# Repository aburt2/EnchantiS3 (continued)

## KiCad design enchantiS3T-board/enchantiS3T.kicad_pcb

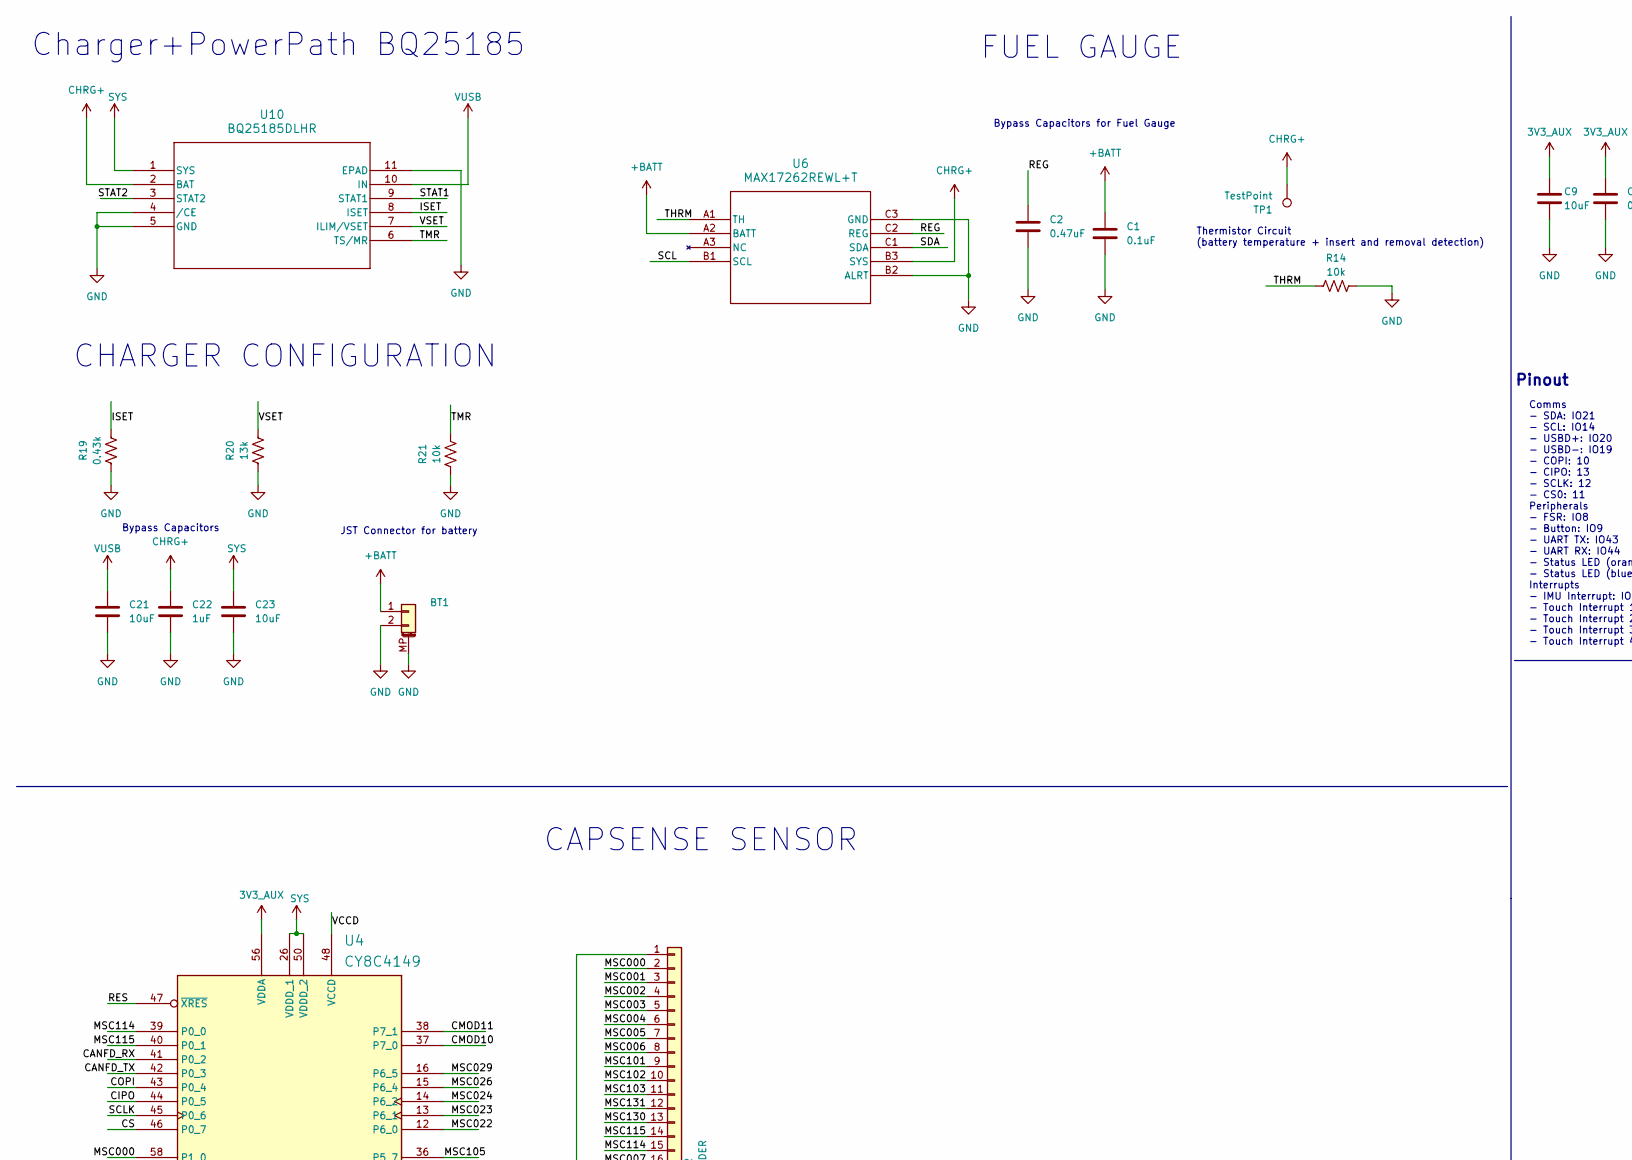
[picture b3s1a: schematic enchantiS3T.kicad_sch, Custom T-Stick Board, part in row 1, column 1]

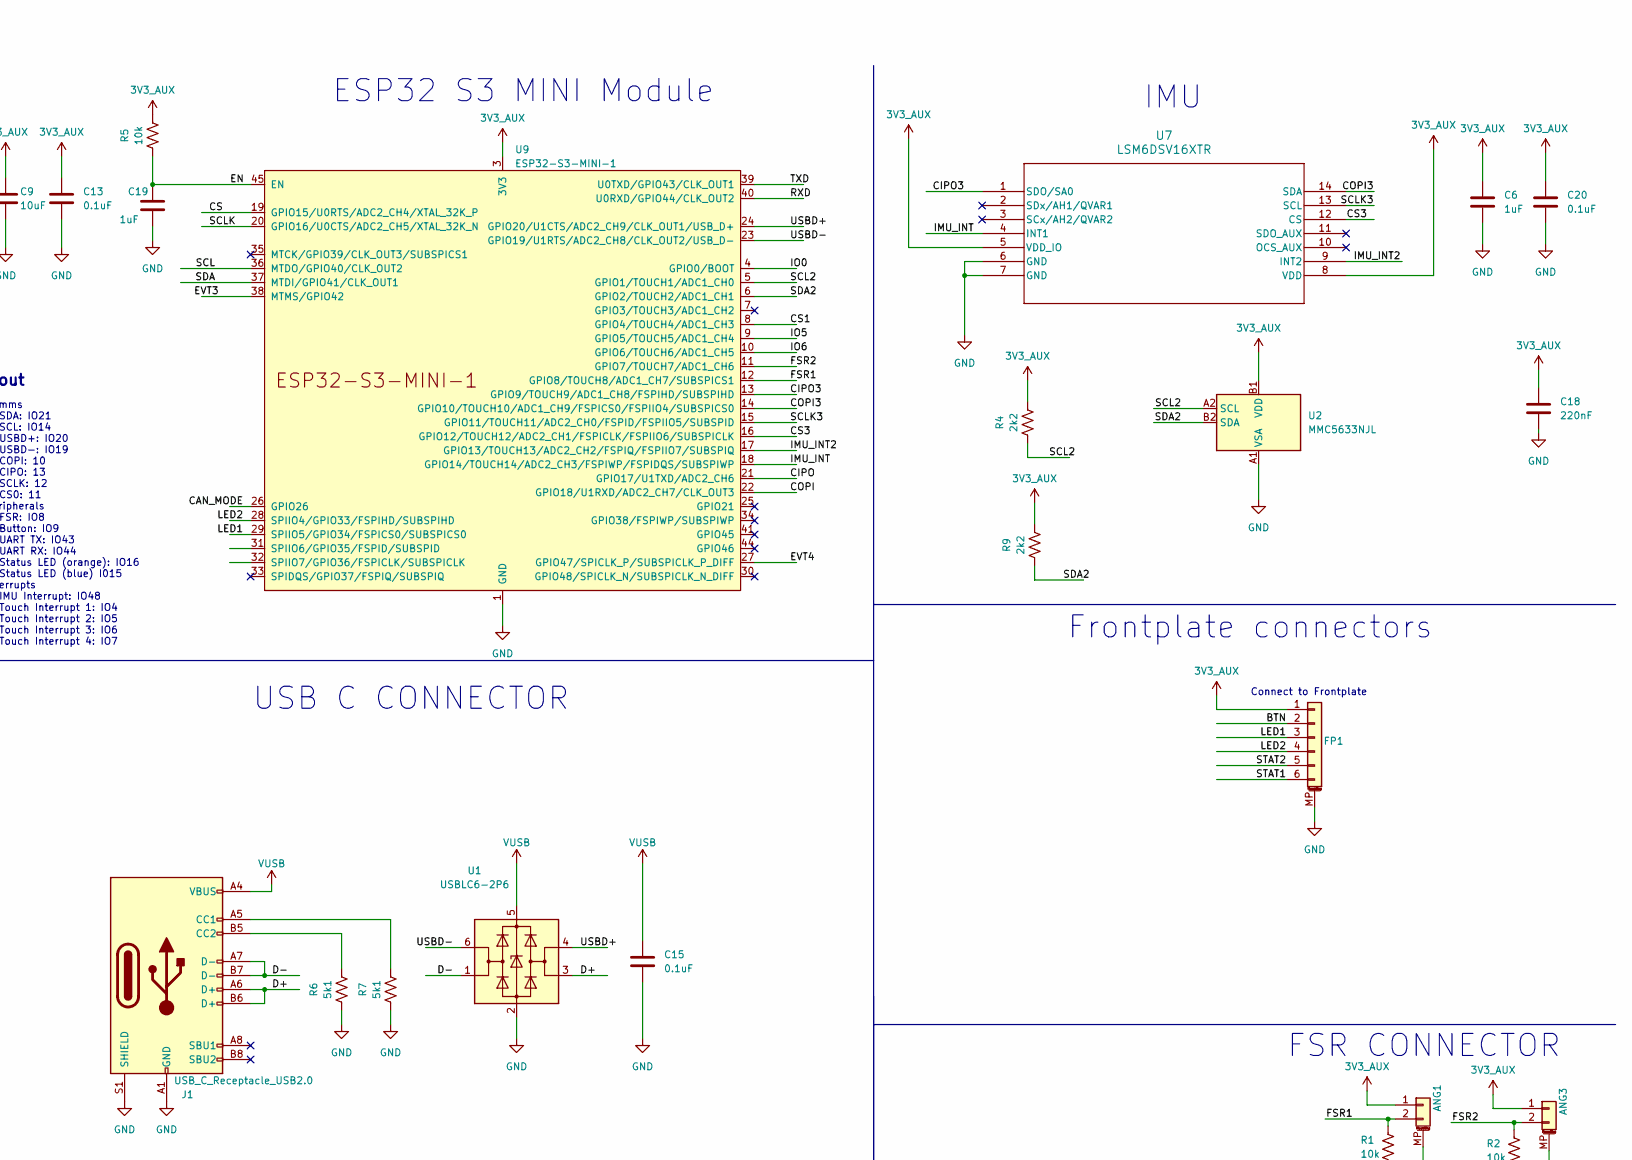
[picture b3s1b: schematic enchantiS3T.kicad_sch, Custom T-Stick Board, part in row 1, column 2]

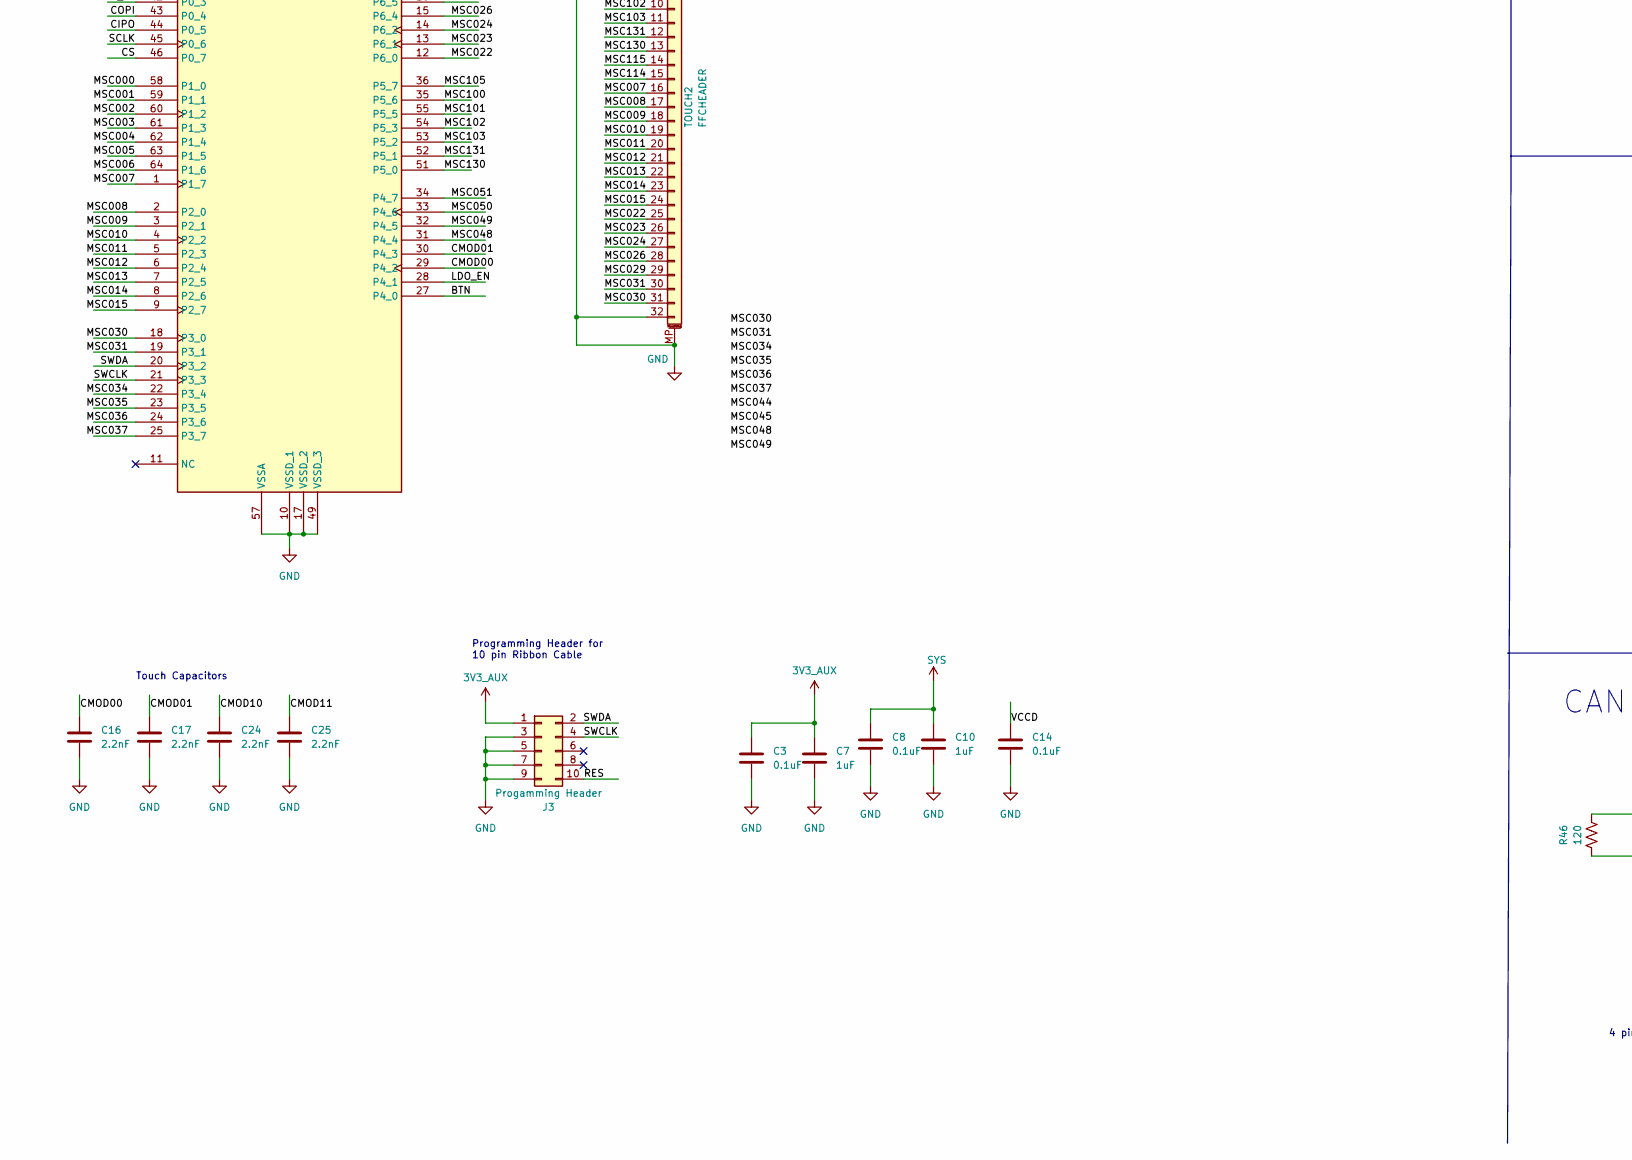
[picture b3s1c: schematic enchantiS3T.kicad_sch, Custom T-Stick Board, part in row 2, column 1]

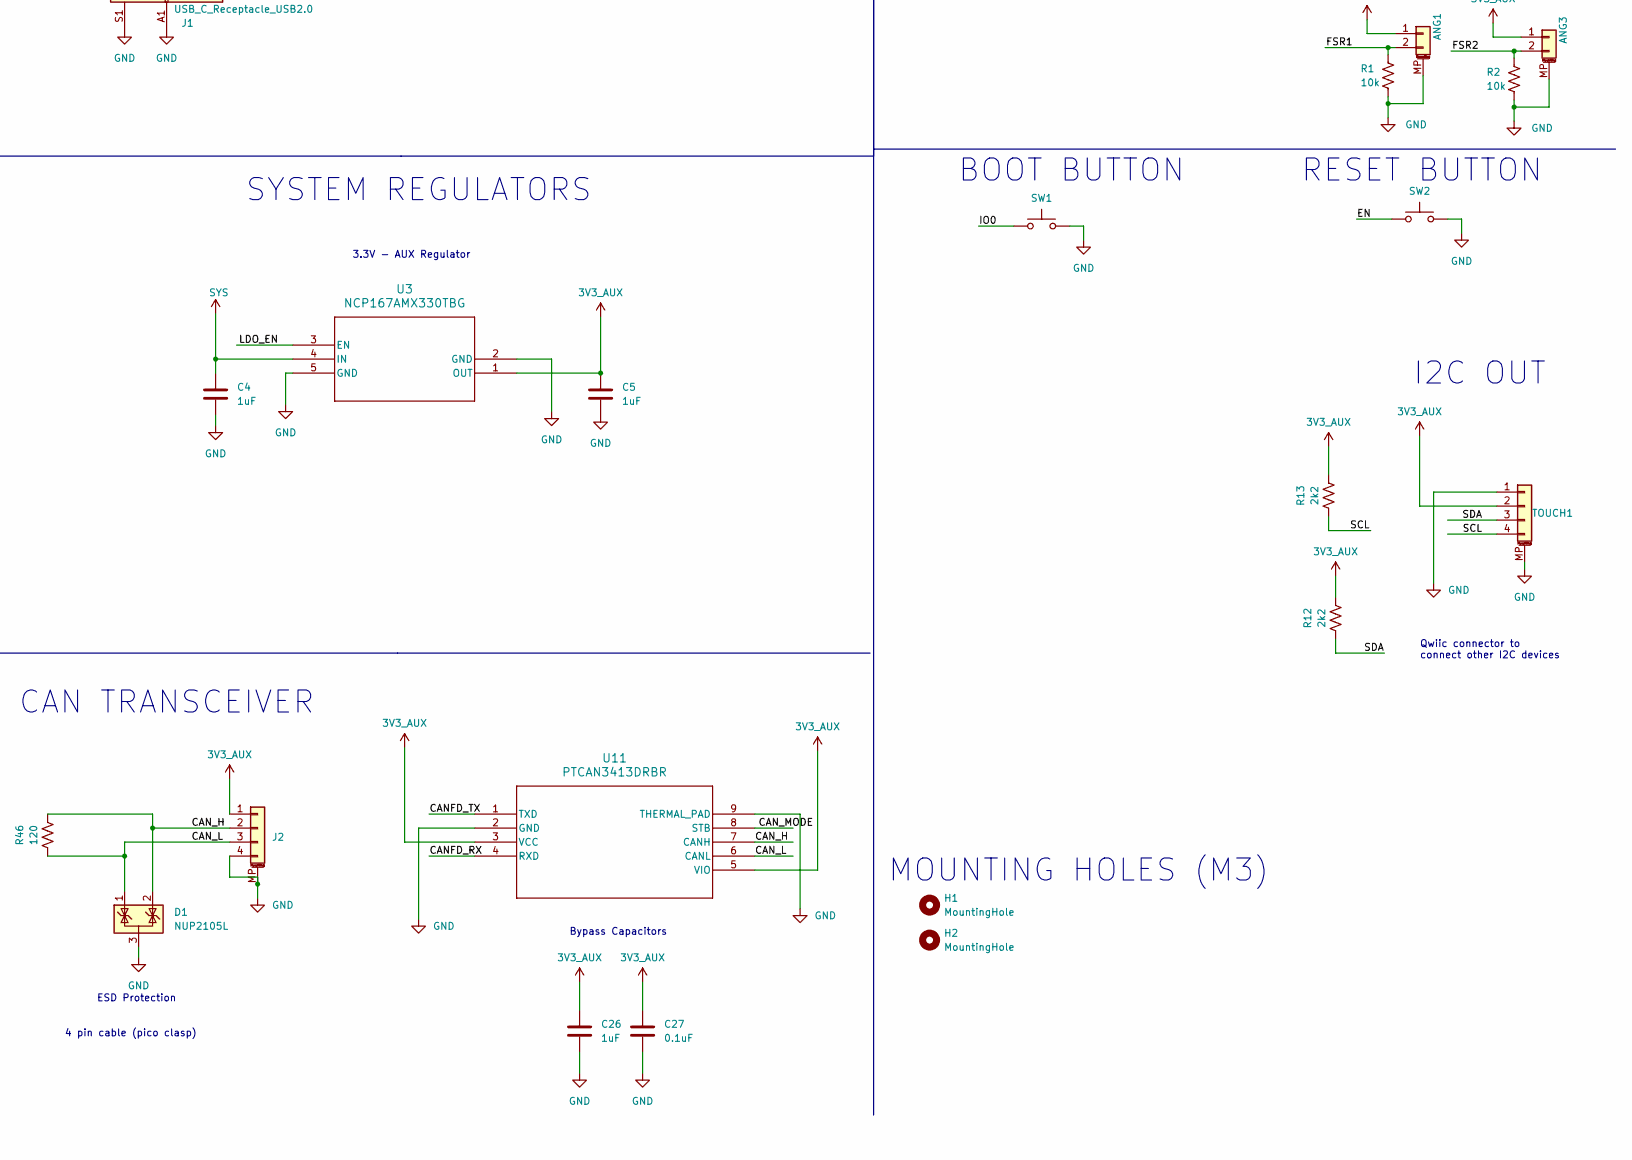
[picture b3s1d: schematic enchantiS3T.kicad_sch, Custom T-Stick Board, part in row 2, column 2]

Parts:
ANG1, ANG3: JST-SH-1.00mm 1x2; JST_SH_BM02B-SRSS-TB_1x02-1MP_P1.00mm_Vertical; Mfg Part # BM02B-SRSS-TB
BT1: JST-PH-1x02-2.000mm; JST_PH_S2B-PH-SM4-TB_1x02-1MP_P2.00mm_Horizontal; Mfg Part # S2B-PH-SM4-TB
C1, C13, C15, C20, C27: 0.1uF; C_0402_1005Metric; Mfg Part # CL05B104KO5NNNC
C2: 0.47uF; C_0402_1005Metric; Mfg Part # GRT155R61C474KE01D
C3, C8, C14: 0.1uF; C_0402_1005Metric; MPN GCM155R71C104KA55J
C4, C5, C6, C19, C22, C26: 1uF; C_0402_1005Metric; Mfg Part # CL05A105KO5NNNC
C7, C10: 1uF; C_0402_1005Metric; MPN GRM155R61C105KA12D
C9, C21, C23: 10uF; C_0603_1608Metric; Mfg Part # CL10A106KO8NNNC
C16, C17, C24, C25: 2.2nF; C_0402_1005Metric; MPN GRM155R71H222JA01J
C18: 220nF; C_0402_1005Metric; Mfg Part # CL05B224KO5NNNC
D1: NUP2105L; SOT-23
FP1: JST-SH-1x04 1.0mm; JST_SH_BM06B-SRSS-TB_1x06-1MP_P1.00mm_Vertical; Mfg Part # BM06B-SRSS-TB
H1, H2: MountingHole; MountingHole_3.2mm_M3_DIN965
J1: USB_C_Receptacle_USB2.0; USB_C_Receptacle_GCT_USB4105-xx-A_16P_TopMnt_Horizontal; Mfg Part # USB4105-GF-A
J2: Conn_01x03_MountingPin; Molex_Pico-Clasp_501331-0407_1x04-1MP_P1.00mm_Vertical
J3: Progamming Header; PinHeader_2x05_P1.27mm_Vertical_SMD; MPN 3220-10-0300-00
R1, R2, R5, R14, R21: 10k; R_0402_1005Metric; Mfg Part # ERJ-2RKF1002X
R4, R9, R12, R13: 2k2; R_0402_1005Metric; Mfg Part # ERJ-2RKF2201X
R6, R7: 5k1; R_0402_1005Metric; Mfg Part # ERJ-2RKF5101X
R19: 0.43k; R_0402_1005Metric; Mfg Part # ERJ-2RKF4300X
R20: 13k; R_0402_1005Metric; Mfg Part # ERJ-2RKF1302X
R46: 120; R_0402_1005Metric; Mfg Part # ERJ-2RKF2201X
SW1, SW2: B3U-1000P; SW_SPST_B3U-1000P; Mfg Part # B3U-1000P
SYS1, SYS3, SYS4, SYS7, SYS8: SYS
TOUCH1: JST-SH-1x04 1.0mm; JST_SH_BM04B-SRSS-TB_1x04-1MP_P1.00mm_Vertical; Mfg Part # BM04B-SRSS-TB
TOUCH2: FFCHEADER; CON_541323262_MOL; MPN 54132-3262
TP1: TestPoint; TestPoint_Pad_D1.0mm
U1: USBLC6-2P6; SOT-666; Mfg Part # USBLC6-2P6
U2: MMC5633NJL; WLP-4_0.86x0.86mm_P0.4mm
U3: NCP167AMX330TBG; XDFN4_1X1_711AJ_ONS
U4: CY8C4149; TQFP50P1200X1200X160-64N
U6: MAX17262REWL+T; 21-100221A_W91G1&plus_3_MXM; Mfg Part # MAX17262REWL+T
U7: LSM6DSV16XTR; LGA14L_LSM6_STM; Mfg Part # LSM6DSV16XTR
U9: ESP32-S3-MINI-1
U10: BQ25185DLHR; WSON10_DLH_TEX-M; Mfg Part # BQ25185DLHR
U11: PTCAN3413DRBR; VSON8-DRB_TEX

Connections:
3V3_AUX: ANG1.1, ANG3.1, C3.2, C5.1, C6.1, C7.2, C9.1, C13.1, C18.1, C20.1, C26.1, C27.1, FP1.1, J2.1, J3.1, R4.2, R5.2, R9.2, R12.2, R13.2, TOUCH1.2, U2.B1 (VDD), U3.1 (OUT), U4.56 (VDDA), U7.5 (VDD_IO), U7.8 (VDD), U9.3 (3V3), U11.3 (VCC), U11.5 (VIO)
+BATT: BT1.1, C1.1, U6.A2 (BATT)
/BTN: FP1.2, U4.27 (P4_0)
/CANFD_RX: U4.41 (P0_2), U11.4 (RXD)
/CANFD_TX: U4.42 (P0_3), U11.1 (TXD)
/CAN_H: D1.2 (K), J2.2, R46.2, U11.7 (CANH)
/CAN_L: D1.1 (K), J2.3, R46.1, U11.6 (CANL)
/CAN_MODE: U9.26 (GPIO26), U11.8 (STB)
/CIPO: U4.44 (P0_5), U9.21 (GPIO17/U1TXD/ADC2_CH6)
/CIPO3: U7.1 (SDO/SA0), U9.13 (GPIO9/TOUCH9/ADC1_CH8/FSPIHD/SUBSPIHD)
/CMOD00: C16.2, U4.29 (P4_2)
/CMOD01: C17.2, U4.30 (P4_3)
/CMOD10: C24.2, U4.37 (P7_0)
/CMOD11: C25.2, U4.38 (P7_1)
/COPI: U4.43 (P0_4), U9.22 (GPIO18/U1RXD/ADC2_CH7/CLK_OUT3)
/COPI3: U7.14 (SDA), U9.14 (GPIO10/TOUCH10/ADC1_CH9/FSPICS0/FSPIIO4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)
/CS: U4.46 (P0_7), U9.19 (GPIO15/U0RTS/ADC2_CH4/XTAL_32K_P)
/CS1: U9.8 (GPIO4/TOUCH4/ADC1_CH3)
/CS3: U7.12 (CS), U9.16 (GPIO12/TOUCH12/ADC2_CH1/FSPICLK/FSPIIO6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)
/D+: J1.A6 (D+), J1.B6 (D+), U1.3 (I/O2)
/D-: J1.A7 (D-), J1.B7 (D-), U1.1 (I/O1)
/EN: C19.1, R5.1, SW2.1, U9.45 (EN)
/EVT3: U9.38 (MTMS/GPIO42)
/EVT4: U9.27 (GPIO47/SPICLK_P/SUBSPICLK_P_DIFF)
/FSR1: ANG1.2, R1.1, U9.12 (GPIO8/TOUCH8/ADC1_CH7/SUBSPICS1)
/FSR2: ANG3.2, R2.1, U9.11 (GPIO7/TOUCH7/ADC1_CH6)
/IMU_INT: U7.4 (INT1), U9.18 (GPIO14/TOUCH14/ADC2_CH3/FSPIWP/FSPIDQS/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)
/IMU_INT2: U7.9 (INT2), U9.17 (GPIO13/TOUCH13/ADC2_CH2/FSPIQ/FSPIIO7/S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)
/IO0: SW1.1, U9.4 (GPIO0/BOOT)
/IO5: U9.9 (GPIO5/TOUCH5/ADC1_CH4)
/IO6: U9.10 (GPIO6/TOUCH6/ADC1_CH5)
/ISET: R19.2, U10.8 (ISET)
/LDO_EN: U3.3 (EN), U4.28 (P4_1)
/LED1: FP1.3, U9.29 (SPIIO5/GPIO34/FSPICS0/SUBSPICS0)
/LED2: FP1.4, U9.28 (SPIIO4/GPIO33/FSPIHD/SUBSPIHD)
/MSC000: TOUCH2.2, U4.58 (P1_0)
/MSC001: TOUCH2.3, U4.59 (P1_1)
/MSC002: TOUCH2.4, U4.60 (P1_2)
/MSC003: TOUCH2.5, U4.61 (P1_3)
/MSC004: TOUCH2.6, U4.62 (P1_4)
/MSC005: TOUCH2.7, U4.63 (P1_5)
/MSC006: TOUCH2.8, U4.64 (P1_6)
/MSC007: TOUCH2.16, U4.1 (P1_7)
/MSC008: TOUCH2.17, U4.2 (P2_0)
/MSC009: TOUCH2.18, U4.3 (P2_1)
/MSC010: TOUCH2.19, U4.4 (P2_2)
/MSC011: TOUCH2.20, U4.5 (P2_3)
/MSC012: TOUCH2.21, U4.6 (P2_4)
/MSC013: TOUCH2.22, U4.7 (P2_5)
/MSC014: TOUCH2.23, U4.8 (P2_6)
/MSC015: TOUCH2.24, U4.9 (P2_7)
/MSC022: TOUCH2.25, U4.12 (P6_0)
/MSC023: TOUCH2.26, U4.13 (P6_1)
/MSC024: TOUCH2.27, U4.14 (P6_2)
/MSC026: TOUCH2.28, U4.15 (P6_4)
/MSC029: TOUCH2.29, U4.16 (P6_5)
/MSC030: TOUCH2.31, U4.18 (P3_0)
/MSC031: TOUCH2.30, U4.19 (P3_1)
/MSC034: U4.22 (P3_4)
/MSC035: U4.23 (P3_5)
/MSC036: U4.24 (P3_6)
/MSC037: U4.25 (P3_7)
/MSC048: U4.31 (P4_4)
/MSC049: U4.32 (P4_5)
/MSC050: U4.33 (P4_6)
/MSC051: U4.34 (P4_7)
/MSC100: U4.35 (P5_6)
/MSC101: TOUCH2.9, U4.55 (P5_5)
/MSC102: TOUCH2.10, U4.54 (P5_3)
/MSC103: TOUCH2.11, U4.53 (P5_2)
/MSC105: U4.36 (P5_7)
/MSC114: TOUCH2.15, U4.39 (P0_0)
/MSC115: TOUCH2.14, U4.40 (P0_1)
/MSC130: TOUCH2.13, U4.51 (P5_0)
/MSC131: TOUCH2.12, U4.52 (P5_1)
/REG: C2.1, U6.C2 (REG)
/RES: J3.10, U4.47 (~XRES)
/RXD: U9.40 (U0RXD/GPIO44/CLK_OUT2)
/SCL: R13.1, TOUCH1.4, U6.B1 (SCL), U9.36 (MTDO/GPIO40/CLK_OUT2)
/SCL2: R4.1, U2.A2 (SCL), U9.5 (GPIO1/TOUCH1/ADC1_CH0)
/SCLK: U4.45 (P0_6), U9.20 (GPIO16/U0CTS/ADC2_CH5/XTAL_32K_N)
/SCLK3: U7.13 (SCL), U9.15 (GPIO11/TOUCH11/ADC2_CH0/FSPID/FSPIIO5/S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)
/SDA: R12.1, TOUCH1.3, U6.C1 (SDA), U9.37 (MTDI/GPIO41/CLK_OUT1)
/SDA2: R9.1, U2.B2 (SDA), U9.6 (GPIO2/TOUCH2/ADC1_CH1)
/STAT1: FP1.6, U10.9 (STAT1)
/STAT2: FP1.5, U10.3 (STAT2)
/SWCLK: J3.4, U4.21 (P3_3)
/SWDA: J3.2, U4.20 (P3_2)
/THRM: R14.1, U6.A1 (TH)
/TMR: R21.2, U10.6 (TS/MR)
/TXD: U9.39 (U0TXD/GPIO43/CLK_OUT1)
/USBD+: U1.4 (I/O2), U9.24 (GPIO20/U1CTS/ADC2_CH9/CLK_OUT1/USB_D+)
/USBD-: U1.6 (I/O1), U9.23 (GPIO19/U1RTS/ADC2_CH8/CLK_OUT2/USB_D-)
/VCCD: C14.2, U4.48 (VCCD)
/VSET: R20.2, U10.7 (ILIM/VSET)
CHRG+: C22.1, TP1.1, U6.B3 (SYS), U10.2 (BAT)
GND: ANG1.MP (MountPin), ANG3.MP (MountPin), BT1.2, BT1.MP (MountPin), C1.2, C2.2, C3.1, C4.2, C5.2, C6.2, C7.1, C8.1, C9.2, C10.1, C13.2, C14.1, C15.2, C16.1, C17.1, C18.2, C19.2, C20.2, C21.2, C22.2, C23.2, C24.1, C25.1, C26.2, C27.2, D1.3 (A), FP1.MP (MountPin), J1.A1 (GND), J1.A12 (GND), J1.B1 (GND), J1.B12 (GND), J1.S1 (SHIELD), J2.4, J2.MP (MountPin), J3.3, J3.5, J3.7, J3.9, R1.2, R2.2, R6.1, R7.1, R14.2, R19.1, R20.1, R21.1, SW1.2, SW2.2, TOUCH1.1, TOUCH1.MP (MountPin), TOUCH2.1, TOUCH2.32, TOUCH2.MP (MountPin), U1.2 (GND), U2.A1 (VSA), U3.2 (GND), U3.5 (GND), U4.10 (VSSD_1), U4.17 (VSSD_2), U4.49 (VSSD_3), U4.57 (VSSA), U6.B2 (ALRT), U6.C3 (GND), U7.6 (GND), U7.7 (GND), U9.1 (GND), U9.2 (GND), U9.42 (GND), U9.43 (GND), U9.46 (GND), U9.47 (GND), U9.48 (GND), U9.49 (GND), U9.50 (GND), U9.51 (GND), U9.52 (GND), U9.53 (GND), U9.54 (GND), U9.55 (GND), U9.56 (GND), U9.57 (GND), U9.58 (GND), U9.59 (GND), U9.60 (GND), U9.61 (GND), U9.62 (GND), U9.63 (GND), U9.64 (GND), U9.65 (GND), U10.4 (/CE), U10.5 (GND), U10.11 (EPAD), U11.2 (GND), U11.9 (THERMAL_PAD)
unnamed: J1.A5 (CC1), R7.2
unnamed: J1.B5 (CC2), R6.2
VUSB: C15.1, C21.1, J1.A4 (VBUS), J1.A9 (VBUS), J1.B4 (VBUS), J1.B9 (VBUS), U1.5 (VBUS), U10.10 (IN)

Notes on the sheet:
USB C CONNECTOR
Comms - SDA: IO21 - SCL: IO14 - USBD+: IO20 - USBD-: IO19 - COPI: 10 - CIPO: 13 - SCLK: 12 - CS0: 11 Peripherals - FSR: IO8 - Button: IO9 - UART TX: IO43 - UART RX: IO44 - Status LED (orange): IO16 - Status LED (blue) I015 Interrupts - IMU Interrupt: IO48 - Touch Interrupt 1: IO4 - Touch Interrupt 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
Qwiic connector to connect other I2C devices
FUEL GAUGE
FSR CONNECTOR
Thermistor Circuit (battery temperature + insert and removal detection)
Programming Header for 10 pin Ribbon Cable
JST Connector for battery
IMU
Bypass Capacitors
Charger+PowerPath BQ25185
I2C OUT
CHARGER CONFIGURATION
Bypass Capacitors
Bypass Capacitors for Fuel Gauge
SYSTEM REGULATORS
3.3V - AUX Regulator
ESP32 S3 MINI Module
MOUNTING HOLES (M3)
Connect to Frontplate
ESD Protection
4 pin cable (pico clasp)
BOOT BUTTON
Pinout
Frontplate connectors
RESET BUTTON
Touch Capacitors
CAN TRANSCEIVER
CAPSENSE SENSOR

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
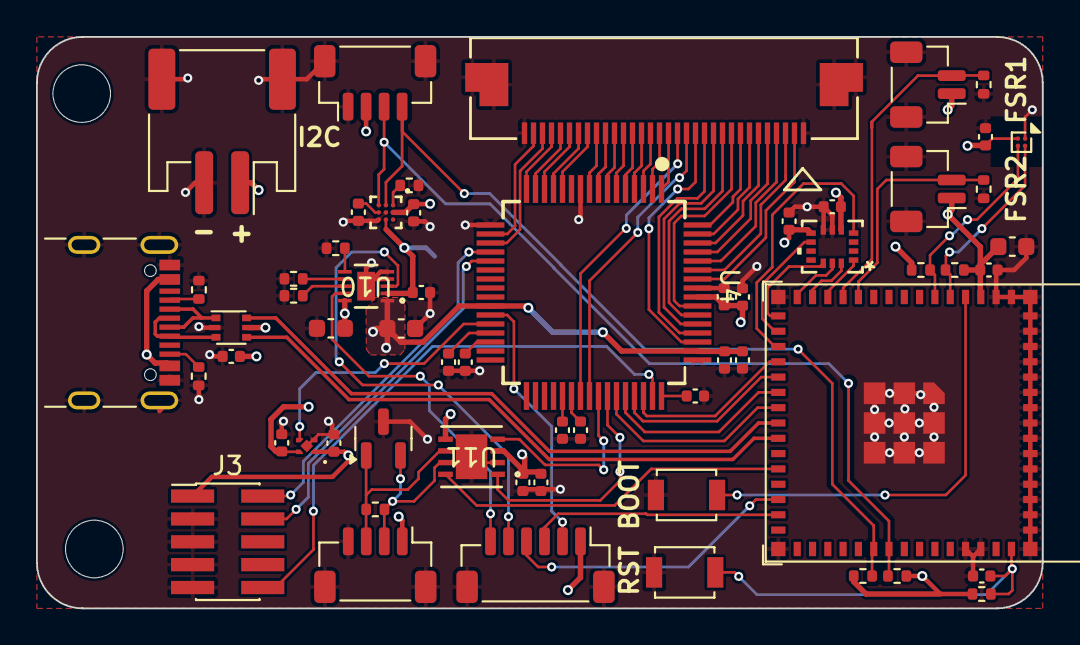
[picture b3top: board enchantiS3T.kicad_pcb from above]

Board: 4 copper layers, 55.9 x 31.8 mm, 63 parts (1 on the bottom side), 84 nets.

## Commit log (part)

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2024-03-30 Update LICENSE
2024-03-30 add the enchantiS3 revision 2 board files
2024-03-30 added revision 3 board design
2024-04-27 switched IMU to LSM6DS16X, changed board to 2 layer, updated passives to 0603 size
2024-04-28 Revert "switched IMU to LSM6DS16X, changed board to 2 layer, updated passives to 0603 size"
    This reverts commit 721c303317f50970347c44c42bf72dd13544c695.
2024-04-28 switched IMU, made USB data traces thicker
2024-04-28 added CAN transreceiver, cleaned up traces, added second jst header for FSR
2024-05-06 changed color of board for 3D viewer
2024-05-23 added IDMIL and McGill logos
2024-05-23 switched battery charged and regulators
2024-05-31 Updated BOM and manufacturing files, removed CAN transceiver, updated silkscreen
2024-06-04 added CIRMMT logo to silkscreen
2024-06-21 fix BOM for revision 3 of the board
2024-06-21 fix incorrect capacitor value in BOM
2024-07-12 updated pullup resistors to 10k
2024-08-11 completed initial routing
2024-08-11 remove schematic lock files
2024-08-13 updated the naming of the boards
2024-08-13 Revert "updated the naming of the boards"
    This reverts commit 0d9db22bb1f35af4bcd5d4db30741dfbccc385c1.
2024-08-13 add enchantiS3T
2024-08-13 reverted back to old board design
2024-08-13 finsished routing for revision 4 of enchantiS3, finished routing for enchantiS3 Touch
2024-08-18 changed name of project to enchanti-module, draft schematic nearly complete
2024-08-31 added usb connector, added leds
2024-09-06 added battery module, initial routing for power and data traces
2024-09-07 added back USB connector, added power path manager, went with smaller connector
2024-09-07 added new symbol for connector
2024-09-09 removed unused nets, simplified connector
2024-09-29 added components to 2S battery charger, changing up the enchanti module design
2024-10-07 Revert "added components to 2S battery charger, changing up the enchanti module design"
    This reverts commit 22a1e749752c1cc608d102de7de6baf7b482e290.
2024-10-07 removed non enchantiS3 files
2024-10-23 updated project to kicad 8.0, switched to using enchantiLibrary footprint/symbols, switched connectors to molex picoclasp, updated imu
2024-10-29 fixed error in BOM, updated prod files
2024-11-08 fixed hole size constraints for pcbway manufacturing, updated frontplate connector,
2024-12-11 remove outdated screenschots
2024-12-30 moved indicator leds
2025-02-25 add sensor fusion testing firmware
2025-03-15 added capsense controller on enchantiS3 board
2025-03-18 updated project to KiCad 9, added touch controller on enchantiS3 board, added canfd bus for connecting additional touch controllers
2025-03-20 removed unused library files, updated manufacturing files for latest board version, added screenshot of schematic
2025-05-24 updated board file
2025-06-02 revert tto two layer board, swap out magnetometer to mmc55983 and fuel gauge to MAX17260
2025-06-02 remove board files to simplify merge
2025-07-07 ignore backups
2025-07-14 Updated BOM info for ESP32 S3 WROOM 2 Module
2025-08-04 Switched to using multi sheet schematic, added NPM1300 to handle power management and WiFi, finished initial PCB layout and routing
2025-08-04 Fixed BOM errors, removed unused Mounting Hole, added rev4 BOM
2025-08-11 Switch to cheaper ESP32S3 WROOM 1 N8R8 Module
2025-08-26 added manufacturing files
